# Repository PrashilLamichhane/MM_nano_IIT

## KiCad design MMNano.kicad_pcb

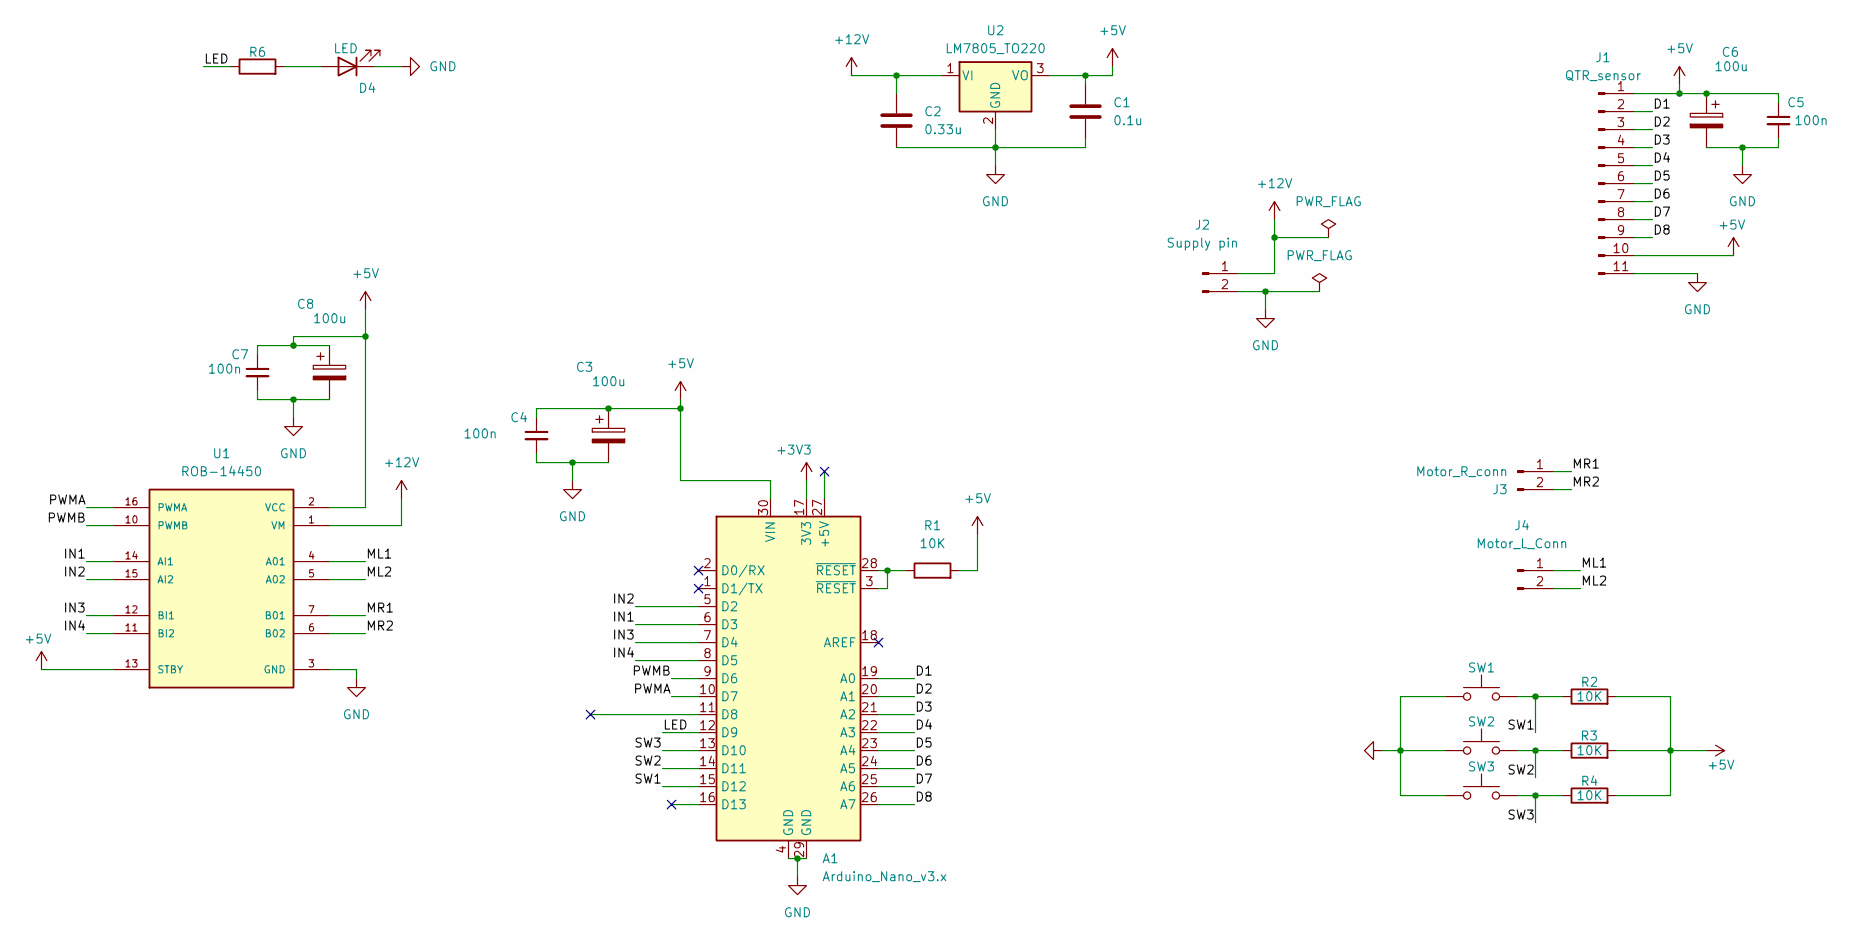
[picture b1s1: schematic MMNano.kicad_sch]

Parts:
A1: Arduino_Nano_v3.x; Arduino_Nano
C1: 0.1u; C_Disc_D3.4mm_W2.1mm_P2.50mm
C2: 0.33u; C_Disc_D3.4mm_W2.1mm_P2.50mm
C3, C6, C8: 100u; CP_Radial_Tantal_D5.0mm_P2.50mm
C4, C5, C7: 100n; C_Disc_D3.4mm_W2.1mm_P2.50mm
D4: LED; LED_D4.0mm
J1: QTR_sensor; PinHeader_1x11_P2.54mm_Vertical
J2: Supply pin; PinHeader_1x02_P2.00mm_Vertical
J3: Motor_R_conn; PinHeader_1x02_P2.00mm_Vertical
J4: Motor_L_Conn; PinHeader_1x02_P2.00mm_Vertical
R1, R2, R3, R4: 10K; R_Axial_DIN0204_L3.6mm_D1.6mm_P5.08mm_Horizontal
R6: R; R_Axial_DIN0204_L3.6mm_D1.6mm_P5.08mm_Horizontal
SW1, SW2, SW3: SW_Push; SW_PUSH_6mm
U1: ROB-14450; MODULE_ROB-14450; PARTREV 11-13-17
U2: LM7805_TO220; TO-220-3_Vertical

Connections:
+3V3: A1.17 (3V3)
+5V: A1.30 (VIN), C1.1, C3.1, C4.1, C5.1, C6.1, C7.1, C8.1, J1.1, J1.10, R1.2, R2.2, R3.2, R4.2, U1.2 (VCC), U1.13 (STBY), U2.3 (VO)
+12V: C2.1, J2.1, U1.1 (VM), U2.1 (VI)
/D1: A1.19 (A0), J1.2
/D2: A1.20 (A1), J1.3
/D3: A1.21 (A2), J1.4
/D4: A1.22 (A3), J1.5
/D5: A1.23 (A4), J1.6
/D6: A1.24 (A5), J1.7
/D7: A1.25 (A6), J1.8
/D8: A1.26 (A7), J1.9
/IN1: A1.6 (D3), U1.14 (AI1)
/IN2: A1.5 (D2), U1.15 (AI2)
/IN3: A1.7 (D4), U1.12 (BI1)
/IN4: A1.8 (D5), U1.11 (BI2)
/LED: A1.12 (D9), R6.1
/ML1: J4.1, U1.4 (A01)
/ML2: J4.2, U1.5 (A02)
/MR1: J3.1, U1.7 (B01)
/MR2: J3.2, U1.6 (B02)
/PWMA: A1.10 (D7), U1.16 (PWMA)
/PWMB: A1.9 (D6), U1.10 (PWMB)
/SW1: A1.15 (D12), R2.1, SW1.2
/SW2: A1.14 (D11), R3.1, SW2.2
/SW3: A1.13 (D10), R4.1, SW3.2
GND: A1.4 (GND), A1.29 (GND), C1.2, C2.2, C3.2, C4.2, C5.2, C6.2, C7.2, C8.2, D4.1 (K), J1.11, J2.2, SW1.1, SW2.1, SW3.1, U1.3 (GND), U1.8 (GND), U1.9 (GND), U2.2 (GND)
unnamed: A1.3 (~RESET), A1.28 (~RESET), R1.1
unnamed: D4.2 (A), R6.2

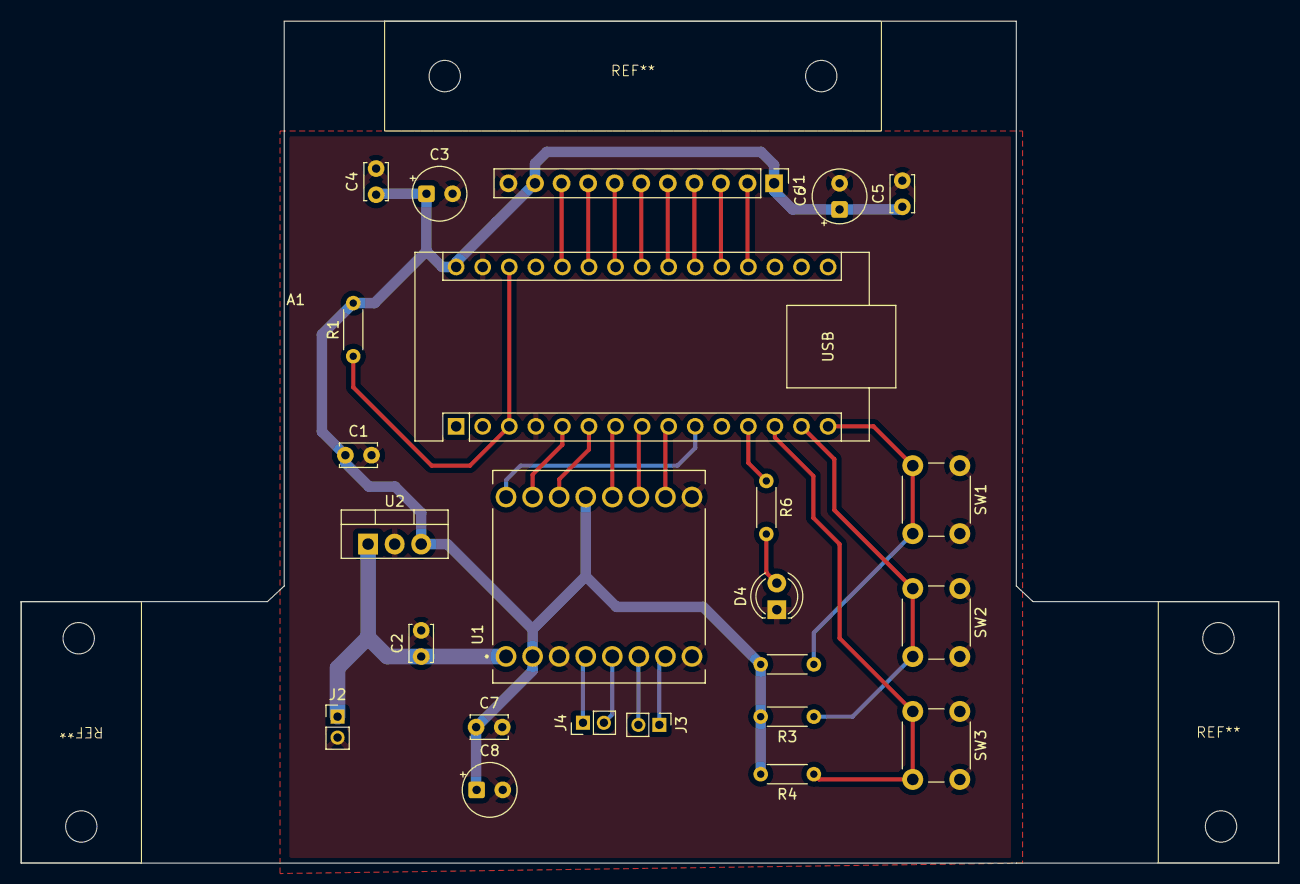
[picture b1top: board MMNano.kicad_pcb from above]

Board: 2 copper layers, 120.2 x 80.5 mm, 24 parts (0 on the bottom side), 27 nets.
